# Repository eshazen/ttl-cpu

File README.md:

# TTL CPU

Yet another TTL CPU.  Inspired by the fact that I have boxes of
leftover TTL chips from the EDF, including a bunch of 74LS181 ALUs.

Also would really like to have a computer I built completely from
scratch at the gate level and which runs some "useful" software.

## Initial thoughts on architecture

* 16-bit address with some possibility of additional paging for expansion
* 16-bit data path, registers, ALU
* Two sizes - DS (8 bit or possibly 16 bit); AS (16 bit)

The design should be completely synchronous.  This implies registers have
a clock enable, so use '377 rather than '374 for example.

| Name | Size | Use                     | Notes                     |
|------|------|-------------------------|---------------------------|
| A    | D    | accumulator.            |                           |
| B    | D    | second operand register |                           |
| X    | A    | index register          |                           |
| SP   | A    | stack pointer           |                           |
| MAR  | A    | memory address register |                           |
| MDR  | D    | memory data register    | Can just use RAM outputs? |
| PC   | A    | program counter         |                           |
| IR   | D    | instruction register    |                           |
| F    | D    | flags                   |                           |

## Control signals

|      |   |                                |
|------|---|--------------------------------|
| LDI  |   | Load IR                        |
|      |   |                                |
| nLDP |   | Load PC                        |
| nENP |   | Output PC                      |
| INP  |   | Increment PC                   |
|      |   |                                |
| LDM  |   | Load MAR                       |
| ENM  |   | Output MAR (MAR always to RAM) |
|      |   |                                |
| MRD  |   | Output RAM (memory read)       |
| MWR  |   | Load RAM (memory write)        |
|      |   |                                |
| IOW  |   | Load IO (IO write)             |
| IOR  |   | Output IO (IO read)            |
|      |   |                                |
| LDB  |   | Load B                         |
| ENB  |   | Output B                       |
|      |   |                                |
| LDA  |   | Load A                         |
| ENA  |   | Output A                       |
|      |   |                                |
| ALE  |   | Output ALU                     |
| ALF  |   | ALU function                   |
|      |   |                                |
| LDX  |   | Load X                         |
| ENX  |   | Output X                       |
|      |   |                                |

## Resources

* [Stack Computers](https://users.ece.cmu.edu/~koopman/stack_computers/index.html):
  the new wave, P. Koopman
* [Figforth.org.uk](http://www.figforth.org.uk/) site with some useful details on the inner workings of FigForth.
* [Systems Guide to FigForth](https://www.forth.org/OffeteStore/1010_SystemsGuideToFigForth.pdf)
* [Starting Forth](https://www.forth.com/starting-forth/0-starting-forth/) by Leo Brodie (online edition)
* [Brad Rodriguez](https://www.bradrodriguez.com/papers/) publications, including an
excellent TCJ series on Forth design
* [TOM-1](https://hackaday.io/project/171965-ttl-operation-module-tom-1)
  project on Hackaday
* [CPUville](http://cpuville.com/index.html) site with various
  including a TTL 8-bit CPU
* [SCAMP](https://github.com/jes/scamp-cpu) CPU project with some
  great software
* ["CPU made out of TTL chips only"](https://www.qsl.net/ct1dmk/ttlcpu.html)
  Another very interesting design.
* [Stack Machine](https://www.mtmscientific.com/stack.html) by MTM Scientific.  Very interesting read.
    * [Eckert paper](Refs/Eckert_paper.html) from 1998, "MICRO-PROGRAMMED VERSUS HARDWIRED CONTROL UNITS:
HOW COMPUTERS REALLY WORK"
* "Practical Digital Design using ICs" by J. Greenfield (available at Internet Archive)
* [fig-FORTH for PDP-11](http://www.stackosaurus.com/figforth.html)

## Tools

There exists https://opencores.org/projects/ttl_library.
The internet says the models work well with GHDL.
This seems the most promising model for simulation.

Found `logisim-evolution`, which is a seemingly competent simulator
with a comprehensive TTL library.  It has testbench support and even
VHDL support.  If it isn't too buggy it could simulate and entire CPU.

Some issues/limitations:

* TTL parts have only "chip icon" representations.  But can wrap them
  as subcircuits.

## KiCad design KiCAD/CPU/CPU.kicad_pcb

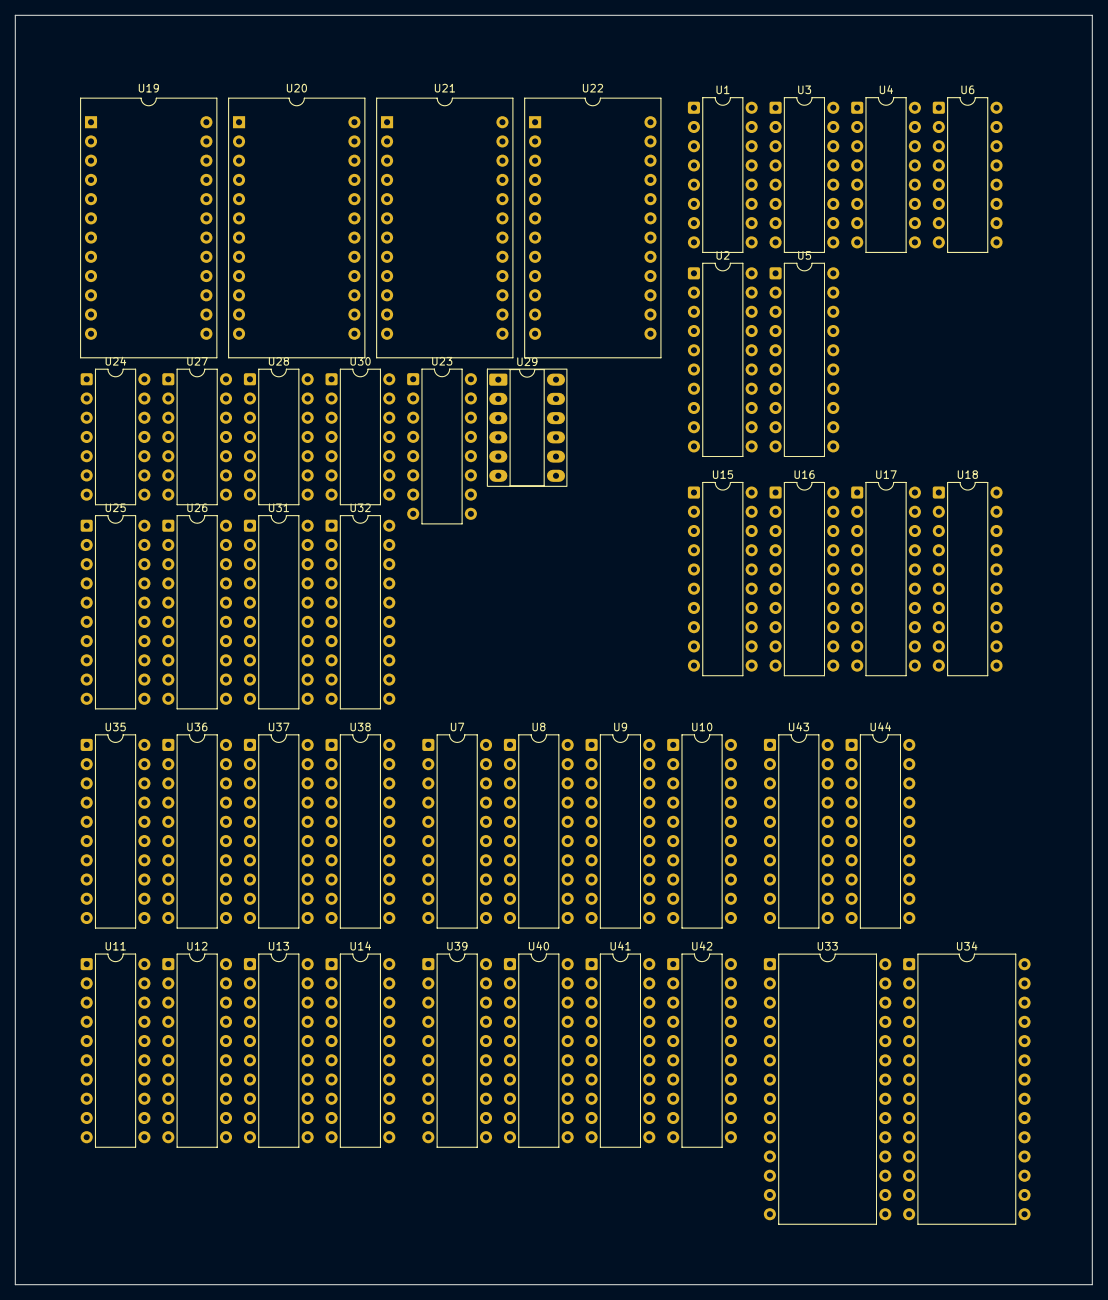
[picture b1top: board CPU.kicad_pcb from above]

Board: 2 copper layers, 142.2 x 167.6 mm, 44 parts (0 on the bottom side), 210 nets, no tracks yet.

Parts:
U1, U3, U4, U6: 74LS163; DIP-16_W7.62mm
U2, U5, U9, U10, U13, U14, U17, U18, U25, U26, U37, U38, U41, U42, U43, U44: 74LS244; DIP-20_W7.62mm
U7, U8, U11, U12, U15, U16, U35, U36, U39, U40: 74LS377; DIP-20_W7.62mm
U19, U20, U21, U22: 74LS181; DIP-24_18.0mmx34.29mm_W15.24mm
U23: 74LS182; DIP-16_W7.62mm
U24: 74LS00; DIP-14_W7.62mm
U27, U28: 74LS86; DIP-14_W7.62mm
U29: 74LS20; DIP-12_W7.62mm_Socket_LongPads
U30: 74LS02; DIP-14_W7.62mm
U31, U32: SN74LS682; DIP-20_W7.62mm
U33, U34: KM62256CLP; DIP-28_W15.24mm

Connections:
/A/D0: U6.3 (D0), U7.3 (D0), U11.3 (D0), U15.3 (D0), U25.18 (O0a), U39.3 (D0), U43.2 (I0a)
/A/D1: U6.4 (D1), U7.4 (D1), U11.4 (D1), U15.4 (D1), U25.16 (O1a), U39.4 (D1), U43.4 (I1a)
/A/D2: U6.5 (D2), U7.7 (D2), U11.7 (D2), U15.7 (D2), U25.14 (O2a), U39.7 (D2), U43.6 (I2a)
/A/D3: U6.6 (D3), U7.8 (D3), U11.8 (D3), U15.8 (D3), U25.12 (O3a), U39.8 (D3), U43.8 (I3a)
/A/D4: U4.3 (D0), U7.13 (D4), U11.13 (D4), U15.13 (D4), U25.9 (O0b), U39.13 (D4), U43.11 (I0b)
/A/D5: U4.4 (D1), U7.14 (D5), U11.14 (D5), U15.14 (D5), U25.7 (O1b), U39.14 (D5), U43.13 (I1b)
/A/D6: U4.5 (D2), U7.17 (D6), U11.17 (D6), U15.17 (D6), U25.5 (O2b), U39.17 (D6), U43.15 (I2b)
/A/D7: U4.6 (D3), U7.18 (D7), U11.18 (D7), U15.18 (D7), U25.3 (O3b), U39.18 (D7), U43.17 (I3b)
/A/D8: U3.3 (D0), U8.3 (D0), U12.3 (D0), U16.3 (D0), U26.18 (O0a), U40.3 (D0), U44.2 (I0a)
/A/D9: U3.4 (D1), U8.4 (D1), U12.4 (D1), U16.4 (D1), U26.16 (O1a), U40.4 (D1), U44.4 (I1a)
/A/D10: U3.5 (D2), U8.7 (D2), U12.7 (D2), U16.7 (D2), U26.14 (O2a), U40.7 (D2), U44.6 (I2a)
/A/D11: U3.6 (D3), U8.8 (D3), U12.8 (D3), U16.8 (D3), U26.12 (O3a), U40.8 (D3), U44.8 (I3a)
/A/D12: U1.3 (D0), U8.13 (D4), U12.13 (D4), U16.13 (D4), U26.9 (O0b), U40.13 (D4), U44.11 (I0b)
/A/D13: U1.4 (D1), U8.14 (D5), U12.14 (D5), U16.14 (D5), U26.7 (O1b), U40.14 (D5), U44.13 (I1b)
/A/D14: U1.5 (D2), U8.17 (D6), U12.17 (D6), U16.17 (D6), U26.5 (O2b), U40.17 (D6), U44.15 (I2b)
/A/D15: U1.6 (D3), U8.18 (D7), U12.18 (D7), U16.18 (D7), U24.2, U26.3 (O3b), U27.2, U40.18 (D7), U44.17 (I3b)
/A/Q0: U13.18 (O0a), U19.1 (B0)
/A/Q1: U13.16 (O1a), U19.22 (B1)
/A/Q2: U13.14 (O2a), U19.20 (B2)
/A/Q3: U13.12 (O3a), U19.18 (B3)
/A/Q4: U13.9 (O0b), U20.1 (B0)
/A/Q5: U13.7 (O1b), U20.22 (B1)
/A/Q6: U13.5 (O2b), U20.20 (B2)
/A/Q7: U13.3 (O3b), U20.18 (B3)
/A/Q8: U14.18 (O0a), U21.1 (B0)
/A/Q9: U14.16 (O1a), U21.22 (B1)
/A/Q10: U14.14 (O2a), U21.20 (B2)
/A/Q11: U14.12 (O3a), U21.18 (B3)
/A/Q12: U14.9 (O0b), U22.1 (B0)
/A/Q13: U14.7 (O1b), U22.22 (B1)
/A/Q14: U14.5 (O2b), U22.20 (B2)
/A/Q15: U14.3 (O3b), U22.18 (B3), U28.1
/ALU/A0: U5.18 (O0a), U17.18 (O0a), U19.2 (A0), U33.11 (Q0), U35.3 (D0), U41.18 (O0a), U43.18 (O0a)
/ALU/A1: U5.16 (O1a), U17.16 (O1a), U19.23 (A1), U33.12 (Q1), U35.4 (D1), U41.16 (O1a), U43.16 (O1a)
/ALU/A2: U5.14 (O2a), U17.14 (O2a), U19.21 (A2), U33.13 (Q2), U35.7 (D2), U41.14 (O2a), U43.14 (O2a)
/ALU/A3: U5.12 (O3a), U17.12 (O3a), U19.19 (A3), U33.15 (Q3), U35.8 (D3), U41.12 (O3a), U43.12 (O3a)
/ALU/A4: U5.9 (O0b), U17.9 (O0b), U20.2 (A0), U33.16 (Q4), U35.13 (D4), U41.9 (O0b), U43.9 (O0b)
/ALU/A5: U5.7 (O1b), U17.7 (O1b), U20.23 (A1), U33.17 (Q5), U35.14 (D5), U41.7 (O1b), U43.7 (O1b)
/ALU/A6: U5.5 (O2b), U17.5 (O2b), U20.21 (A2), U33.18 (Q6), U35.17 (D6), U41.5 (O2b), U43.5 (O2b)
/ALU/A7: U5.3 (O3b), U17.3 (O3b), U20.19 (A3), U33.19 (Q7), U35.18 (D7), U41.3 (O3b), U43.3 (O3b)
/ALU/A8: U2.18 (O0a), U18.18 (O0a), U21.2 (A0), U34.11 (Q0), U36.3 (D0), U42.18 (O0a), U44.18 (O0a)
/ALU/A9: U2.16 (O1a), U18.16 (O1a), U21.23 (A1), U34.12 (Q1), U36.4 (D1), U42.16 (O1a), U44.16 (O1a)
/ALU/A10: U2.14 (O2a), U18.14 (O2a), U21.21 (A2), U34.13 (Q2), U36.7 (D2), U42.14 (O2a), U44.14 (O2a)
/ALU/A11: U2.12 (O3a), U18.12 (O3a), U21.19 (A3), U34.15 (Q3), U36.8 (D3), U42.12 (O3a), U44.12 (O3a)
/ALU/A12: U2.9 (O0b), U18.9 (O0b), U22.2 (A0), U34.16 (Q4), U36.13 (D4), U42.9 (O0b), U44.9 (O0b)
/ALU/A13: U2.7 (O1b), U18.7 (O1b), U22.23 (A1), U34.17 (Q5), U36.14 (D5), U42.7 (O1b), U44.7 (O1b)
/ALU/A14: U2.5 (O2b), U18.5 (O2b), U22.21 (A2), U34.18 (Q6), U36.17 (D6), U42.5 (O2b), U44.5 (O2b)
/ALU/A15: U2.3 (O3b), U18.3 (O3b), U22.19 (A3), U27.1, U34.19 (Q7), U36.18 (D7), U42.3 (O3b), U44.3 (O3b)
/ALU/CN+X: U20.7 (Cn), U23.12 (Cn+x)
/ALU/CN+Y: U21.7 (Cn), U23.11 (Cn+y)
/ALU/CN+Z: U22.7 (Cn), U23.9 (Cn+z)
/ALU/EQ0: U19.14 (A=B), U29.1
/ALU/EQ1: U20.14 (A=B), U29.2
/ALU/EQ2: U21.14 (A=B), U29.4
/ALU/EQH: U30.3, U32.18 (~P=Q)
/ALU/EQL: U30.2, U31.18 (~P=Q)
/ALU/F0: U19.9 (F0), U25.2 (I0a), U31.2 (P0)
/ALU/F1: U19.10 (F1), U25.4 (I1a), U31.4 (P1)
/ALU/F2: U19.11 (F2), U25.6 (I2a), U31.6 (P2)
/ALU/F3: U19.13 (F3), U25.8 (I3a), U31.8 (P3)
/ALU/F4: U20.9 (F0), U25.11 (I0b), U31.11 (P4)
/ALU/F5: U20.10 (F1), U25.13 (I1b), U31.13 (P5)
/ALU/F6: U20.11 (F2), U25.15 (I2b), U31.15 (P6)
/ALU/F7: U20.13 (F3), U25.17 (I3b), U31.17 (P7)
/ALU/F8: U21.9 (F0), U26.2 (I0a), U32.2 (P0)
/ALU/F9: U21.10 (F1), U26.4 (I1a), U32.4 (P1)
/ALU/F10: U21.11 (F2), U26.6 (I2a), U32.6 (P2)
/ALU/F11: U21.13 (F3), U26.8 (I3a), U32.8 (P3)
/ALU/F12: U22.9 (F0), U26.11 (I0b), U32.11 (P4)
/ALU/F13: U22.10 (F1), U26.13 (I1b), U32.13 (P5)
/ALU/F14: U22.11 (F2), U26.15 (I2b), U32.15 (P6)
/ALU/F15: U22.13 (F3), U26.17 (I3b), U32.17 (P7)
/ALU_S0: U19.6 (S0), U20.6 (S0), U21.6 (S0), U22.6 (S0)
/ALU_S1: U19.5 (S1), U20.5 (S1), U21.5 (S1), U22.5 (S1)
/ALU_S2: U19.4 (S2), U20.4 (S2), U21.4 (S2), U22.4 (S2)
/ALU_S3: U19.3 (S3), U20.3 (S3), U21.3 (S3), U22.3 (S3)
/MAR/Q0: U9.18 (O0a), U33.10 (A0), U34.10 (A0)
/MAR/Q1: U9.16 (O1a), U33.9 (A1), U34.9 (A1)
/MAR/Q2: U9.14 (O2a), U33.8 (A2), U34.8 (A2)
/MAR/Q3: U9.12 (O3a), U33.7 (A3), U34.7 (A3)
/MAR/Q4: U9.9 (O0b), U33.6 (A4), U34.6 (A4)
/MAR/Q5: U9.7 (O1b), U33.5 (A5), U34.5 (A5)
/MAR/Q6: U9.5 (O2b), U33.4 (A6), U34.4 (A6)
/MAR/Q7: U9.3 (O3b), U33.3 (A7), U34.3 (A7)
/MAR/Q8: U10.18 (O0a), U33.25 (A8), U34.25 (A8)
/MAR/Q9: U10.16 (O1a), U33.24 (A9), U34.24 (A9)
/MAR/Q10: U10.14 (O2a), U33.21 (A10), U34.21 (A10)
/MAR/Q11: U10.12 (O3a), U33.23 (A11), U34.23 (A11)
/MAR/Q12: U10.9 (O0b), U33.2 (A12), U34.2 (A12)
/MAR/Q13: U10.7 (O1b), U33.26 (A13), U34.26 (A13)
/MAR/Q14: U10.5 (O2b), U33.1 (A14), U34.1 (A14)
/MODE: U19.8 (M), U20.8 (M), U21.8 (M), U22.8 (M)
/~ALU2B: U43.1 (OEa), U43.19 (OEb), U44.1 (OEa), U44.19 (OEb)
/~ALU_OE: U25.1 (OEa), U25.19 (OEb), U26.1 (OEa), U26.19 (OEb)
/~A_EN: U11.1 (~E), U12.1 (~E)
/~B_EN: U15.1 (~E), U16.1 (~E)
/~B_OE: U17.1 (OEa), U17.19 (OEb), U18.1 (OEa), U18.19 (OEb)
/~C_EN: U39.1 (~E), U40.1 (~E)
/~C_OE: U41.1 (OEa), U41.19 (OEb), U42.1 (OEa), U42.19 (OEb)
/~IR_EN: U35.1 (~E), U36.1 (~E)
/~IR_OE: U37.1 (OEa), U37.19 (OEb), U38.1 (OEa), U38.19 (OEb)
/~MAR_EN: U7.1 (~E), U8.1 (~E)
/~PC_INC: U1.7 (CEP), U3.7 (CEP), U4.7 (CEP), U6.7 (CEP), U6.10 (CET)
/~PC_LD: U1.9 (~PE), U3.9 (~PE), U4.9 (~PE), U6.9 (~PE)
/~PC_OE: U2.1 (OEa), U2.19 (OEb), U5.1 (OEa), U5.19 (OEb)
/~RAM_OE: U33.22 (~OE), U34.22 (~OE)
/~RAM_WE: U33.27 (~WE), U34.27 (~WE)
CLK: U1.2 (CP), U3.2 (CP), U4.2 (CP), U6.2 (CP), U7.11 (CP), U8.11 (CP), U11.11 (CP), U12.11 (CP), U15.11 (CP), U16.11 (CP), U35.11 (CP), U36.11 (CP), U39.11 (CP), U40.11 (CP)
GND: U1.8 (GND), U2.10 (GND), U3.8 (GND), U4.8 (GND), U5.10 (GND), U6.8 (GND), U7.10 (GND), U8.10 (GND), U9.1 (OEa), U9.10 (GND), U9.19 (OEb), U10.1 (OEa), U10.10 (GND), U10.19 (OEb), U11.10 (GND), U12.10 (GND), U13.1 (OEa), U13.10 (GND), U13.19 (OEb), U14.1 (OEa), U14.10 (GND), U14.19 (OEb), U15.10 (GND), U16.10 (GND), U17.10 (GND), U18.10 (GND), U19.12 (GND), U20.12 (GND), U21.12 (GND), U22.12 (GND), U23.8 (GND), U25.10 (GND), U26.10 (GND), U31.3 (Q0), U31.5 (Q1), U31.7 (Q2), U31.9 (Q3), U31.10 (GND), U31.12 (Q4), U31.14 (Q5), U31.16 (Q6), U32.3 (Q0), U32.5 (Q1), U32.7 (Q2), U32.9 (Q3), U32.10 (GND), U32.12 (Q4), U32.14 (Q5), U32.16 (Q6), U33.14 (GND), U33.20 (~CS), U34.14 (GND), U34.20 (~CS), U35.10 (GND), U36.10 (GND), U37.10 (GND), U38.10 (GND), U39.10 (GND), U40.10 (GND), U41.10 (GND), U42.10 (GND), U43.10 (GND), U44.10 (GND)
unnamed: U1.10 (CET), U3.15 (TC)
unnamed: U1.14 (Q0), U2.11 (I0b)
unnamed: U1.13 (Q1), U2.13 (I1b)
unnamed: U1.12 (Q2), U2.15 (I2b)
unnamed: U1.11 (Q3), U2.17 (I3b)
unnamed: U2.2 (I0a), U3.14 (Q0)
unnamed: U2.4 (I1a), U3.13 (Q1)
unnamed: U2.6 (I2a), U3.12 (Q2)
unnamed: U2.8 (I3a), U3.11 (Q3)
unnamed: U3.10 (CET), U4.15 (TC)
unnamed: U4.10 (CET), U6.15 (TC)
unnamed: U4.14 (Q0), U5.11 (I0b)
unnamed: U4.13 (Q1), U5.13 (I1b)
unnamed: U4.12 (Q2), U5.15 (I2b)
unnamed: U4.11 (Q3), U5.17 (I3b)
unnamed: U5.2 (I0a), U6.14 (Q0)
unnamed: U5.4 (I1a), U6.13 (Q1)
unnamed: U5.6 (I2a), U6.12 (Q2)
unnamed: U5.8 (I3a), U6.11 (Q3)
unnamed: U7.6 (Q2), U9.6 (I2a)
unnamed: U7.9 (Q3), U9.8 (I3a)
unnamed: U7.12 (Q4), U9.11 (I0b)
unnamed: U7.15 (Q5), U9.13 (I1b)
unnamed: U7.16 (Q6), U9.15 (I2b)
unnamed: U7.19 (Q7), U9.17 (I3b)
unnamed: U8.2 (Q0), U10.2 (I0a)
unnamed: U8.12 (Q4), U10.11 (I0b)
unnamed: U8.5 (Q1), U10.4 (I1a)
unnamed: U8.15 (Q5), U10.13 (I1b)
unnamed: U8.6 (Q2), U10.6 (I2a)
unnamed: U8.16 (Q6), U10.15 (I2b)
unnamed: U8.9 (Q3), U10.8 (I3a)
unnamed: U8.19 (Q7), U10.17 (I3b)
unnamed: U11.6 (Q2), U13.6 (I2a)
unnamed: U11.9 (Q3), U13.8 (I3a)
unnamed: U11.12 (Q4), U13.11 (I0b)
unnamed: U11.15 (Q5), U13.13 (I1b)
unnamed: U11.16 (Q6), U13.15 (I2b)
unnamed: U11.19 (Q7), U13.17 (I3b)
unnamed: U12.2 (Q0), U14.2 (I0a)
unnamed: U12.5 (Q1), U14.4 (I1a)
unnamed: U12.6 (Q2), U14.6 (I2a)
unnamed: U12.9 (Q3), U14.8 (I3a)
unnamed: U12.12 (Q4), U14.11 (I0b)
unnamed: U12.15 (Q5), U14.13 (I1b)
unnamed: U12.16 (Q6), U14.15 (I2b)
unnamed: U12.19 (Q7), U14.17 (I3b)
unnamed: U15.6 (Q2), U17.6 (I2a)
unnamed: U15.9 (Q3), U17.8 (I3a)
unnamed: U15.12 (Q4), U17.11 (I0b)
unnamed: U15.15 (Q5), U17.13 (I1b)
unnamed: U15.16 (Q6), U17.15 (I2b)
unnamed: U15.19 (Q7), U17.17 (I3b)
unnamed: U16.2 (Q0), U18.2 (I0a)
unnamed: U16.5 (Q1), U18.4 (I1a)
unnamed: U16.6 (Q2), U18.6 (I2a)
unnamed: U16.9 (Q3), U18.8 (I3a)
unnamed: U16.12 (Q4), U18.11 (I0b)
unnamed: U16.15 (Q5), U18.13 (I1b)
unnamed: U16.16 (Q6), U18.15 (I2b)
unnamed: U16.19 (Q7), U18.17 (I3b)
unnamed: U19.15 (X), U23.4 (P0)
unnamed: U19.17 (Y), U23.3 (G0)
unnamed: U20.15 (X), U23.2 (P1)
unnamed: U20.17 (Y), U23.1 (G1)
unnamed: U21.15 (X), U23.15 (P2)
unnamed: U21.17 (Y), U23.14 (G2)
unnamed: U22.15 (X), U23.6 (P3)
unnamed: U22.17 (Y), U23.5 (G3)
unnamed: U24.3, U28.2
unnamed: U24.4, U27.3
unnamed: U24.5, U28.3
unnamed: U35.6 (Q2), U37.6 (I2a)
unnamed: U35.9 (Q3), U37.8 (I3a)
unnamed: U35.12 (Q4), U37.11 (I0b)
unnamed: U35.15 (Q5), U37.13 (I1b)
unnamed: U35.16 (Q6), U37.15 (I2b)
unnamed: U35.19 (Q7), U37.17 (I3b)
unnamed: U36.2 (Q0), U38.2 (I0a)
unnamed: U36.5 (Q1), U38.4 (I1a)
unnamed: U36.6 (Q2), U38.6 (I2a)
unnamed: U36.9 (Q3), U38.8 (I3a)
unnamed: U36.12 (Q4), U38.11 (I0b)
unnamed: U36.15 (Q5), U38.13 (I1b)
unnamed: U36.16 (Q6), U38.15 (I2b)
unnamed: U36.19 (Q7), U38.17 (I3b)
unnamed: U39.6 (Q2), U41.6 (I2a)
unnamed: U39.9 (Q3), U41.8 (I3a)
unnamed: U39.12 (Q4), U41.11 (I0b)
unnamed: U39.15 (Q5), U41.13 (I1b)
unnamed: U39.16 (Q6), U41.15 (I2b)
unnamed: U39.19 (Q7), U41.17 (I3b)
unnamed: U40.2 (Q0), U42.2 (I0a)
unnamed: U40.5 (Q1), U42.4 (I1a)
unnamed: U40.6 (Q2), U42.6 (I2a)
unnamed: U40.9 (Q3), U42.8 (I3a)
unnamed: U40.12 (Q4), U42.11 (I0b)
unnamed: U40.15 (Q5), U42.13 (I1b)
unnamed: U40.16 (Q6), U42.15 (I2b)
unnamed: U40.19 (Q7), U42.17 (I3b)
VCC: U1.1 (~MR), U1.16 (VCC), U2.20 (VCC), U3.1 (~MR), U3.16 (VCC), U4.1 (~MR), U4.16 (VCC), U5.20 (VCC), U6.1 (~MR), U6.16 (VCC), U7.20 (VCC), U8.20 (VCC), U9.20 (VCC), U10.20 (VCC), U11.20 (VCC), U12.20 (VCC), U13.20 (VCC), U14.20 (VCC), U15.20 (VCC), U16.20 (VCC), U17.20 (VCC), U18.20 (VCC), U19.24 (VCC), U20.24 (VCC), U21.24 (VCC), U22.24 (VCC), U23.13 (Cn), U23.16 (VCC), U24.1, U25.20 (VCC), U26.20 (VCC), U31.20 (VCC), U32.20 (VCC), U33.28 (VCC), U34.28 (VCC), U35.20 (VCC), U36.20 (VCC), U37.20 (VCC), U38.20 (VCC), U39.20 (VCC), U40.20 (VCC), U41.20 (VCC), U42.20 (VCC), U43.20 (VCC), U44.20 (VCC)

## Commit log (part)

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2026-05-21 Create repo
2026-05-21 readme
2026-05-23 Add Stack Machine link to README
2026-05-24 starting on schematic
2026-05-26 docs
2026-05-27 TIL stuff
2026-06-18 add some labels
